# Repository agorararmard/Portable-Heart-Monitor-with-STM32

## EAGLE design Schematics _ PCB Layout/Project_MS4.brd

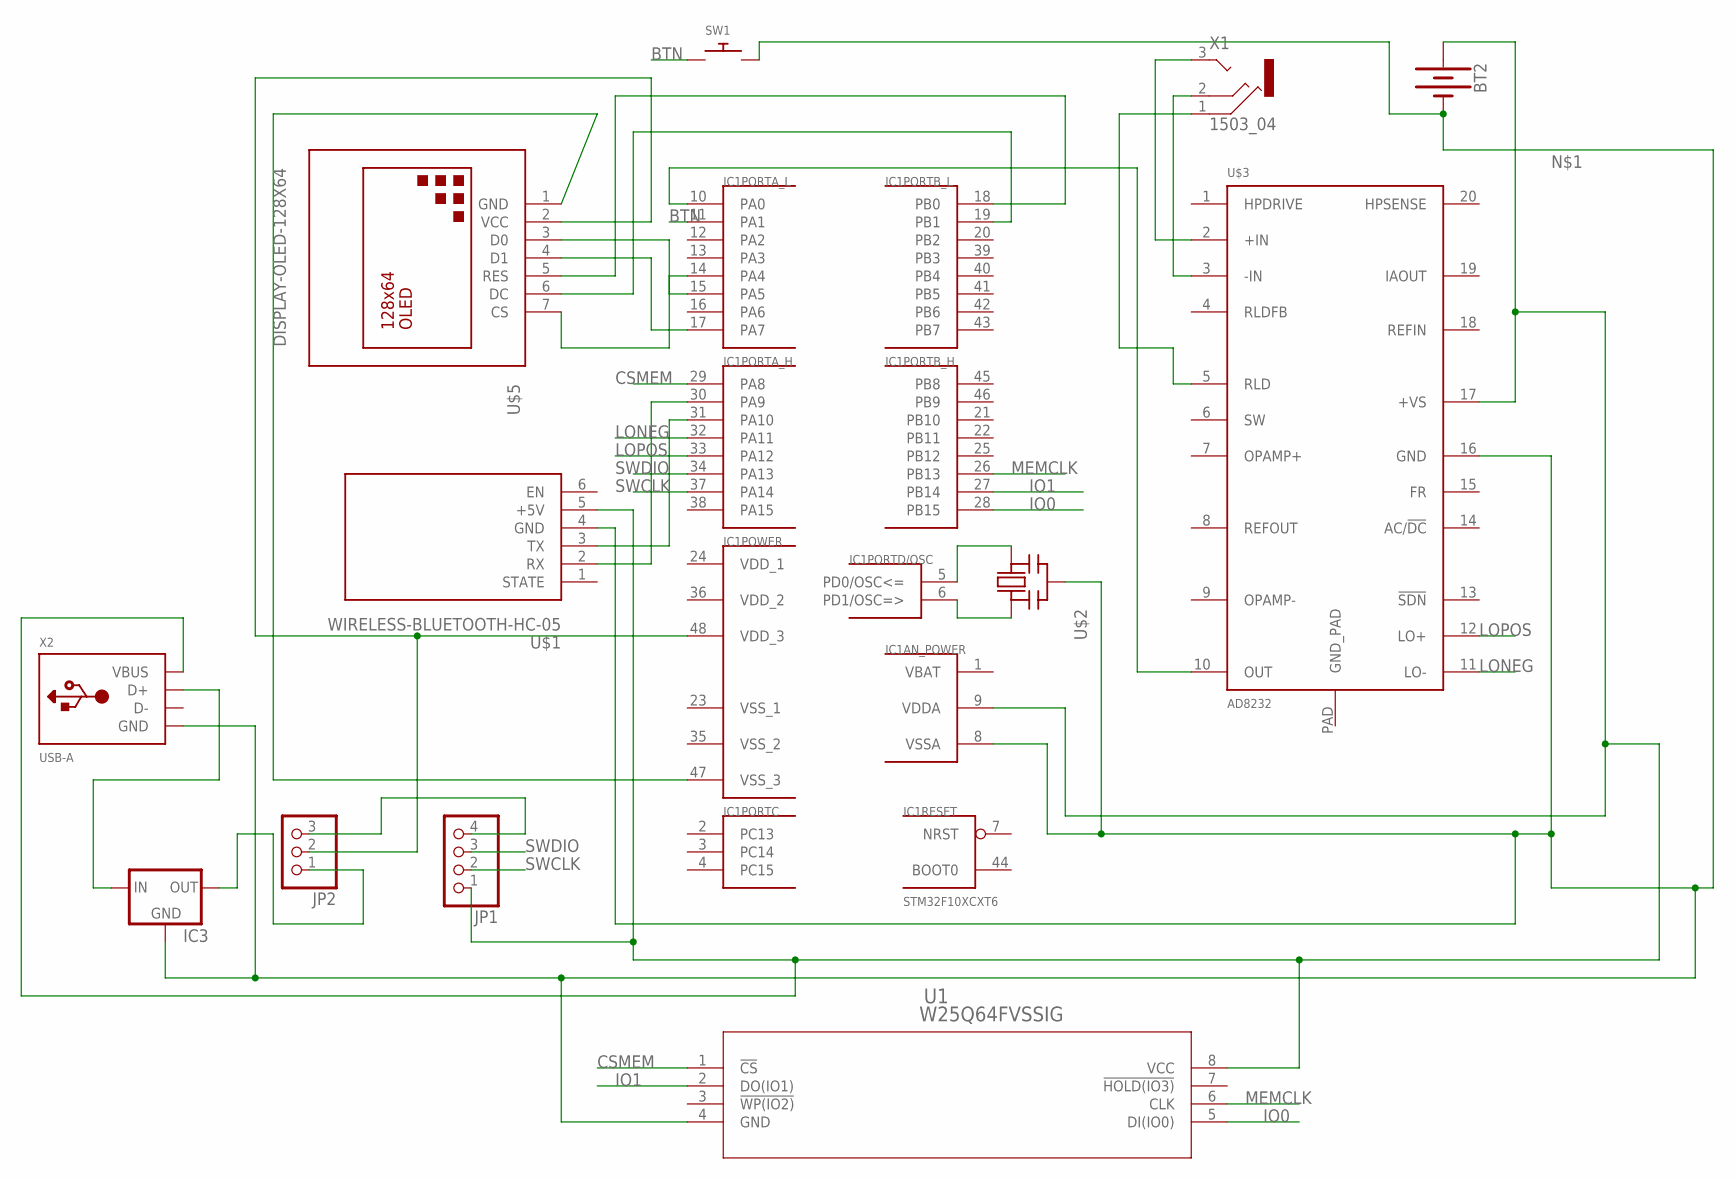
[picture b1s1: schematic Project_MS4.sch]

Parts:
BT2: BATTERY-AAA_KIT; BATTERY-AAA-KIT
IC1: STM32F10XCXT6; TQFP48
IC3: MCP1700INLINE; TO92-INLINE
JP1: PINHD-1X4; 1X04
JP2: PINHD-1X3; 1X03
SW1: SWITCH_PUSHBUTTONC&K_KSS; BTN_CK_KSS
U1: W25Q64FVSSIG; WIN_SS-8
U$1: WIRELESS-BLUETOOTH-HC-05
U$2: CERMOSCILL-AWCSR; AWCSR
U$3: AD8232; LFCSP_20
U$5: DISPLAY-OLED-128X64
X1: 1503_04
X2: USB-A; MOLEX_480371000

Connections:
BTN: IC1.11 (PA1), SW1.P$1
CSMEM: IC1.29 (PA8), U1.1 (!CS)
IO0: IC1.28 (PB15), U1.5 (DI(IO0))
IO1: IC1.27 (PB14), U1.2 (DO(IO1))
LONEG: IC1.32 (PA11), U$3.11 (LO-)
LOPOS: IC1.33 (PA12), U$3.12 (LO+)
MEMCLK: IC1.26 (PB13), U1.6 (CLK)
unnamed: BT2.PWR@1 (+), IC1.9 (VDDA), JP1.1, U1.8 (VCC), U$1.5 (+5V), U$3.17 (+VS), X2.1 (VBUS)
unnamed: IC1.10 (PA0), U$3.10 (OUT)
unnamed: IC1.19 (PB1), U$5.6 (DC)
unnamed: IC1.14 (PA4), U$5.7 (CS)
unnamed: IC1.17 (PA7), U$5.4 (D1)
unnamed: IC1.15 (PA5), U$5.3 (D0)
unnamed: IC1.47 (VSS_3), U$5.1 (GND)
unnamed: JP1.4, JP2.3
unnamed: IC1.48 (VDD_3), JP2.2, U$5.2 (VCC)
unnamed: IC3.3 (OUT), JP2.1
unnamed: U$3.5 (RLD), X1.1
unnamed: U$3.3 (-IN), X1.2 (3)
unnamed: IC1.18 (PB0), U$5.5 (RES)
unnamed: U$3.2 (+IN), X1.3 (2)
unnamed: IC3.2 (IN), X2.3 (D+)
unnamed: IC1.6 (PD1/OSC=>), U$2.1 (IN)
unnamed: IC1.5 (PD0/OSC<=), U$2.3 (OUT)
unnamed: IC1.30 (PA9), U$1.2 (RX)
unnamed: IC1.31 (PA10), U$1.3 (TX)
unnamed: BT2.GND@1 (-), IC1.8 (VSSA), IC3.1 (GND), SW1.P$2, U1.4 (GND), U$1.4 (GND), U$2.2 (GND), U$3.16 (GND), X2.4 (GND)
SWCLK: IC1.37 (PA14), JP1.2
SWDIO: IC1.34 (PA13), JP1.3
VBAT: IC1.1 (VBAT)
VDD_1: IC1.24 (VDD_1)
VDD_2: IC1.36 (VDD_2)
VSS_1: IC1.23 (VSS_1)
VSS_2: IC1.35 (VSS_2)

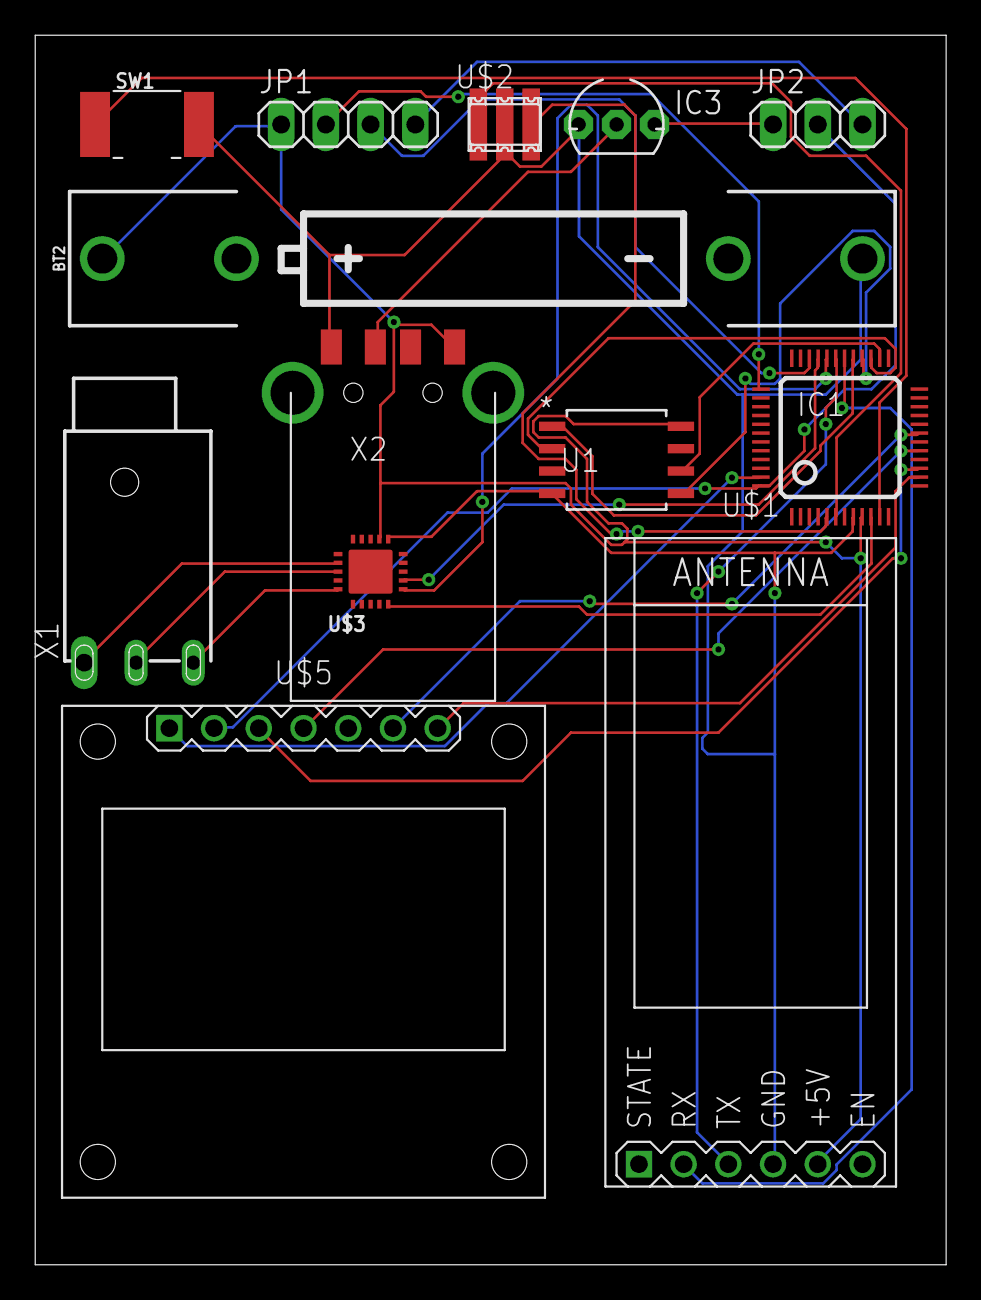
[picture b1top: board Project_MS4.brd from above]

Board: 2 copper layers, 51.7 x 69.8 mm, 13 parts (0 on the bottom side), 29 nets.

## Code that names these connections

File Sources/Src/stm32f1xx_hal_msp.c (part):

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    __HAL_RCC_ADC1_CLK_ENABLE();
  
    /**ADC1 GPIO Configuration    
    PA0-WKUP     ------> ADC1_IN0 
    */
    GPIO_InitStruct.Pin = adcPin_Pin;
    GPIO_InitStruct.Mode = GPIO_MODE_ANALOG;
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    __HAL_RCC_ADC1_CLK_DISABLE();
  
    /**ADC1 GPIO Configuration    
    PA0-WKUP     ------> ADC1_IN0 
    */
    HAL_GPIO_DeInit(adcPin_GPIO_Port, adcPin_Pin);

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    __HAL_RCC_SPI1_CLK_ENABLE();
  
    /**SPI1 GPIO Configuration    
    PA4     ------> SPI1_NSS
    PA5     ------> SPI1_SCK
    PA6     ------> SPI1_MISO
    PA7     ------> SPI1_MOSI 
    */
    GPIO_InitStruct.Pin = selectionPin_Pin|spiClk_Pin|spiMosi_Pin;
    GPIO_InitStruct.Mode = GPIO_MODE_AF_PP;
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    __HAL_RCC_SPI2_CLK_ENABLE();
  
    /**SPI2 GPIO Configuration    
    PB13     ------> SPI2_SCK
    PB14     ------> SPI2_MISO
    PB15     ------> SPI2_MOSI 
    */
    GPIO_InitStruct.Pin = GPIO_PIN_13|GPIO_PIN_15;
    GPIO_InitStruct.Mode = GPIO_MODE_AF_PP;
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    __HAL_RCC_SPI1_CLK_DISABLE();
  
    /**SPI1 GPIO Configuration    
    PA4     ------> SPI1_NSS
    PA5     ------> SPI1_SCK
    PA6     ------> SPI1_MISO
    PA7     ------> SPI1_MOSI 
    */
    HAL_GPIO_DeInit(GPIOA, selectionPin_Pin|spiClk_Pin|spiMiso_Pin|spiMosi_Pin);

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    __HAL_RCC_SPI2_CLK_DISABLE();
  
    /**SPI2 GPIO Configuration    
    PB13     ------> SPI2_SCK
    PB14     ------> SPI2_MISO
    PB15     ------> SPI2_MOSI 
    */
    HAL_GPIO_DeInit(GPIOB, GPIO_PIN_13|GPIO_PIN_14|GPIO_PIN_15);

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    __HAL_RCC_USART1_CLK_ENABLE();
  
    /**USART1 GPIO Configuration    
    PA9     ------> USART1_TX
    PA10     ------> USART1_RX 
    */
    GPIO_InitStruct.Pin = txPin_Pin;
    GPIO_InitStruct.Mode = GPIO_MODE_AF_PP;
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    __HAL_RCC_USART1_CLK_DISABLE();
  
    /**USART1 GPIO Configuration    
    PA9     ------> USART1_TX
    PA10     ------> USART1_RX 
    */
    HAL_GPIO_DeInit(GPIOA, txPin_Pin|rxPin_Pin);

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
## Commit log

2019-09-30 Developed Code

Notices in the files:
Sources/Src/stm32f1xx_hal_msp.c:
Copyright (c) 2019 STMicroelectronics International N.V.
All rights reserved.
(C) COPYRIGHT STMicroelectronics *****END OF FILE
parts and their libraries:
SparkFun-Batteries: Licensing: Creative Commons ShareAlike 4.0 International - https://creativecommons.org/licenses/by-sa/4.0
diy-modules: Released under the Creative Commons Attribution 4.0 International License: http://creativecommons.org/licenses/by/4.0
